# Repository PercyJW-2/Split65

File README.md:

# Split65
Split 65 Percent Keyboard

## Features
- ProMicro and Proton C support
- QMK Port
- Hot-Swap
- I2C support (not implemented in QMK-Port)

## Instructions
- when using an Proton C
  - R2 needs to be populated with an Resistor with an value of 3k3 up to 6k8
  - R3 needs to be populated with an resistor with an value of 100
- when using an ProMicro
  - R3 needs to be shorted
- when using I2C
  - R1 and R2 need to be populated with an apropriate Resistor
  - both jumpers need to be shorted

## Images

### Left

### Right

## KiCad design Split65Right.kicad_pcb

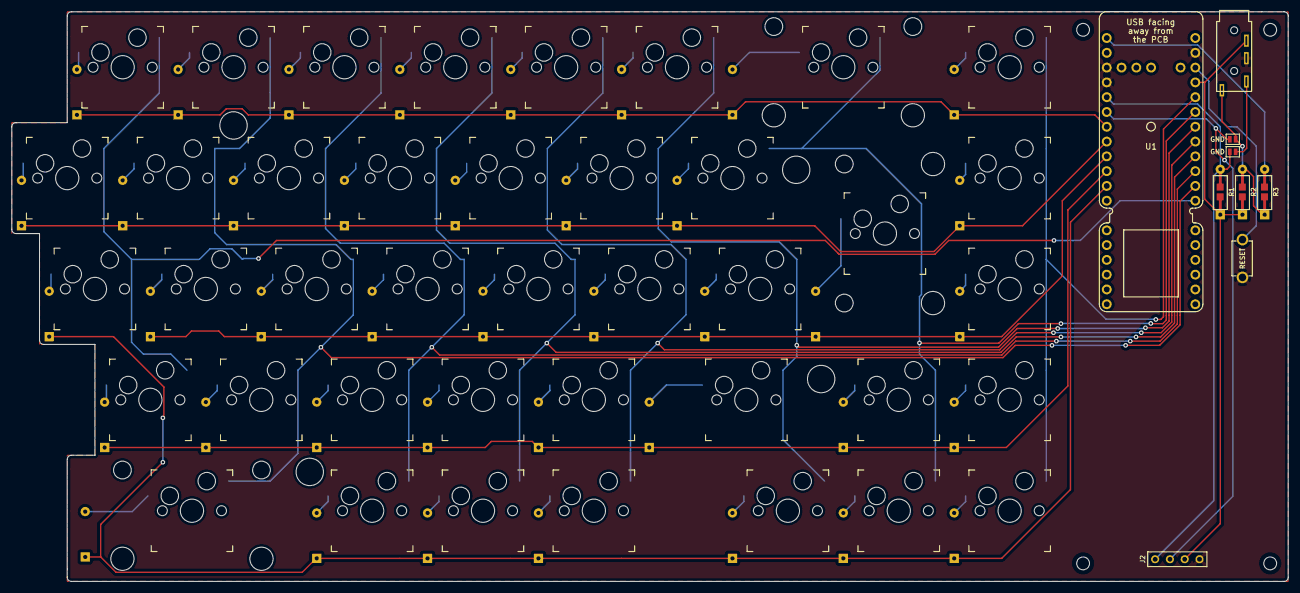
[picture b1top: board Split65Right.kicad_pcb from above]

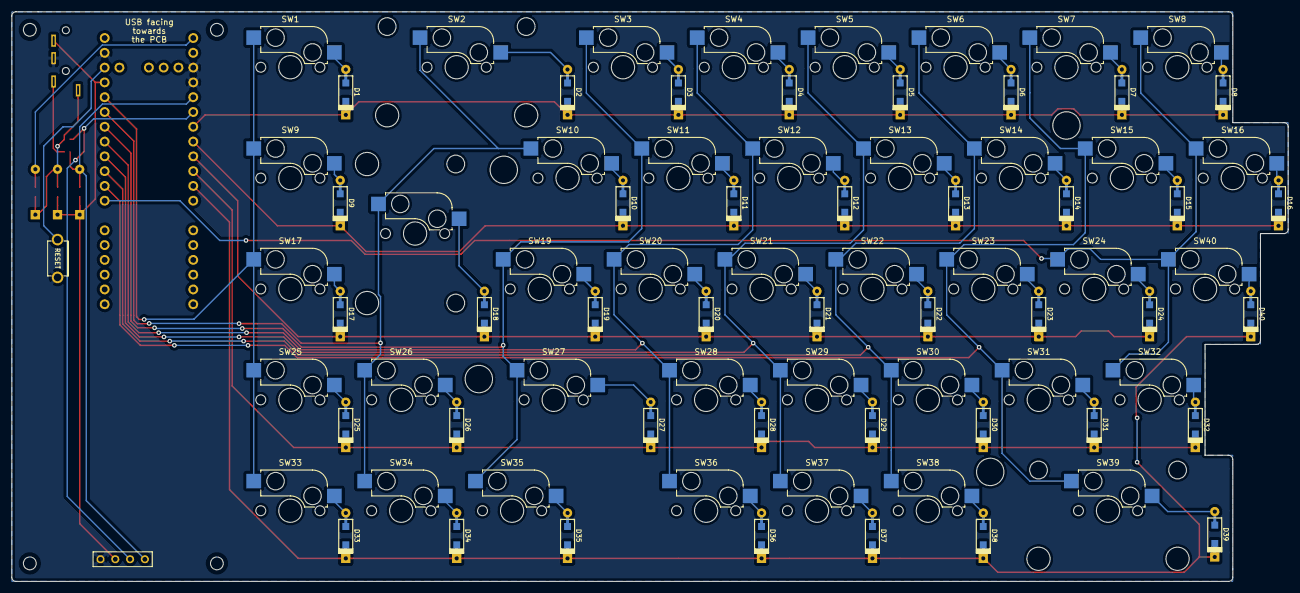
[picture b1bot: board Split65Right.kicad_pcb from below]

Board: 2 copper layers, 219.2 x 97.8 mm, 97 parts (40 on the bottom side), 60 nets.

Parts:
D1, D2, D3, D4, D5, D6, D7, D8, D9, D10, D11, D12, D13, D14, D15, D16, D17, D18, D19, D20, D21, D22, D23, D24, D25, D26, D27, D28, D29, D30, D31, D32, D33, D34, D35, D36, D37, D38, D39, D40: D; D_SOD123_axial
HOLE_3M, HOLE_3M#2, HOLE_3M#3, HOLE_3M#4: VAL**; HOLE_M2_TH
HOLE_M2, HOLE_M2#2, HOLE_M2#3, HOLE_M2#4: VAL**; HOLE_M2
J1: Jack4; TRRS_JACK_MJ4PP9
J2: OLED; OLED_4Pin
JP2, JP3: GND; Jumper
R1, R2: 5k; R_1608_axial
R3: 120; R_1608_axial
SW1, SW3, SW4, SW5, SW6, SW7, SW8, SW9, SW10, SW11, SW12, SW13, SW14, SW15, SW16, SW17, SW19, SW20, SW21, SW22, SW23, SW24, SW25, SW26, SW28, SW29, SW30, SW31, SW32, SW33, SW34, SW35, SW36, SW37, SW38, SW40: SW_PUSH; KailhSocket-1U
SW2: SW_PUSH; KailhSocket-2U
SW18: SW_PUSH; KailhSocket-ISO
SW27: SW_PUSH; KailhSocket-1.75U
SW39: SW_PUSH; KailhSocket-2.25U
SW_41: SW_Push; TACT_SWITCH_TVBP06
U1: Proton_C; proton_c

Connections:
+3V3: J2.3, R1.1, R2.1, U1.3.3V
COL0: SW1.1, SW9.1, SW17.1, SW25.1, SW33.1, U1.A2
COL1: SW2.1, SW10.1, SW18.1, SW26.1, SW34.1, U1.A1
COL2: SW3.1, SW11.1, SW19.1, SW27.1, SW35.1, U1.A0
COL3: SW4.1, SW12.1, SW20.1, SW28.1, SW36.1, U1.B8
COL4: SW5.1, SW13.1, SW21.1, SW29.1, SW37.1, U1.B13
COL5: SW6.1, SW14.1, SW22.1, SW30.1, SW38.1, U1.B14
COL6: SW7.1, SW15.1, SW23.1, SW31.1, SW39.1, U1.B15
COL7: SW8.1, SW16.1, SW24.1, SW32.1, SW40.1, U1.B9
DATA: R3.2, U1.A9
GND: J1.C, J2.4, SW_41.1, U1.GND
unnamed: D1.2, SW1.2
unnamed: D2.2, SW2.2
unnamed: D3.2, SW3.2
unnamed: D4.2, SW4.2
unnamed: D5.2, SW5.2
unnamed: D6.2, SW6.2
unnamed: D7.2, SW7.2
unnamed: D8.2, SW8.2
unnamed: D9.2, SW9.2
unnamed: D10.2, SW10.2
unnamed: D11.2, SW11.2
unnamed: D12.2, SW12.2
unnamed: D13.2, SW13.2
unnamed: D14.2, SW14.2
unnamed: D15.2, SW15.2
unnamed: D16.2, SW16.2
unnamed: D17.2, SW17.2
unnamed: D18.2, SW18.2
unnamed: D19.2, SW19.2
unnamed: D20.2, SW20.2
unnamed: D21.2, SW21.2
unnamed: D22.2, SW22.2
unnamed: D23.2, SW23.2
unnamed: D24.2, SW24.2
unnamed: D25.2, SW25.2
unnamed: D26.2, SW26.2
unnamed: D27.2, SW27.2
unnamed: D28.2, SW28.2
unnamed: D29.2, SW29.2
unnamed: D30.2, SW30.2
unnamed: D31.2, SW31.2
unnamed: D32.2, SW32.2
unnamed: D33.2, SW33.2
unnamed: D34.2, SW34.2
unnamed: D35.2, SW35.2
unnamed: D36.2, SW36.2
unnamed: D37.2, SW37.2
unnamed: D38.2, SW38.2
unnamed: D39.2, SW39.2
unnamed: D40.2, SW40.2
unnamed: JP3.1, R2.2, R3.1
RESET: SW_41.2, U1.DFU
ROW0: D1.1, D2.1, D3.1, D4.1, D5.1, D6.1, D7.1, D8.1, U1.B5
ROW1: D9.1, D10.1, D11.1, D12.1, D13.1, D14.1, D15.1, D16.1, U1.B4
ROW2: D17.1, D18.1, D19.1, D20.1, D21.1, D22.1, D23.1, D24.1, U1.B3
ROW3: D25.1, D26.1, D27.1, D28.1, D29.1, D30.1, D31.1, D32.1, U1.B2
ROW4: D33.1, D34.1, D35.1, D36.1, D37.1, D38.1, D39.1, D40.1, U1.B1
SCL: J2.2, JP3.2, U1.B6
SDA: J2.1, JP2.2, R1.2, U1.B7

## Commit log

2020-10-04 modified: Split65Left-cache.lib modified: Split65Left.kicad_pcb modified: Split65Left.kicad_pcb-bak modified: Split65Left.net modified: Split65Left.sch modified: Split65Left.sch-bak modified: Split65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
2020-10-10 Added Plates for left side
2020-11-05 Updated some small things - removed 3u buttons
2020-11-12 removed wrongly scaled dxf files deleted: BackPlateLeft.dxf deleted: BackPlateRight.dxf modified: ../fp-info-cache
2021-06-20 Fixed Critical Error: Ground between the two halves was not connected
2021-06-20 updated gerber files
2021-06-20 add picture
